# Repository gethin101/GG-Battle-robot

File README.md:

# Gethin's Custom BATTLE ROBOT
**This is my custom Robot Wars inspired battle robot with a servo-driven axe weapon, wireless radio frequency remote control, LCD display, RGB lights, and audio sound effects. My robot is controlled by a custom PCB RF remote using a Raspberry Pi Pico H microcontroller running CircuitPython and the chassis and axe will be 3D printed in PLA.**

It runs on a Raspberry pi pico H, TT motors, L298N motor drivers, and a servo motor. It is controlled by a 433mhz radio frequency remote, another Raspberry pi pico H, a joystick module and extra control buttons. The 2 main axe weapons and chassis will be 3d printed in PLA.

I am also using a 1.8" SPI LCD Display for the robot to display information on the front of the robot and SK6812 MINI-E RGB leds for the back of the robot. These will both be powered by being plugged into the breadboard in the robot using the pins and jumper wires.

Also I have sound effects for my robot. I will do this through a PAM8302 amplifier board and 8Ω 2W speaker. The amplifier board will go into the breadboard & the speaker will plug directly into the PAM8302.

**It is powered by AA batteries, the actual robot will be connected using a breadboard & jumper wires, but I wanted to create a custom PCB for my remote. I designed the PCB in KiCad, also with female sockets so I can remove modules from the remote.**

**Note:** I had to connect the grounds on either side together so they have the same voltage reference point.

My weapon system consists of a servo motor embedded on the underside of the top half of the chassis that will swing the PLA axe weapon down to hit, and back up to rest on the slanted design of the robot.

---

## Inspiration
I wanted to make this project to help me learn CAD design through Fusion 360, PCB design in KiCad and get me into the world of electronics and embedded systems.
I designed my robot with inspiration from Thor in Robot Wars with the axe weapon idea and Apollo with the general shape and aesthetics

---

## Control

I control my robot through the use of the PCB remote. There is a joystick module that with the use of the RF transmitter, will control the TT motors on the robot and therefore the movement of the wheels. 

I have also added a button on the remote to control the servo motor that moves the PLA axe weapon and also a few buttons that play sound effects and display custom data on the display.

---

## **Remote PCB:**

**Solder:**
- Battery wires to copper pad
- Pico through hole
- Buttons

**Headers:**
- RF module
- Joystick
- Boost converter

Remote PCB design:

**This was my first PCB design before I made it in KiCad**

I then designed my remote PCB in KiCad with the schematic below showing how all the components are connected:

**PCB design process:**

I designed my remote PCB in KiCad. I made through-hole pins for the pico where I will have the choice to either solder on female headers which will allow easy removal of the pico for the remote or to directly solder them on. 
This took some time to design as I wasn't sure on which approach would better fit my project, so I left it for my decision when I get the parts.

Next, I added 3 small buttons that I will solder straight onto the PCB. These will be used as control buttons for the robot where I will program them to sent certains signals to the robot, for example to move the axe head up or down with the servo motor, or to carry out pre-programmed movement plans with the TT motors and wheels.

I added two copper pads for the battery+ and battery- to my PCB to power the remote and I ended up decising to put these on the back side of the PCB so it leaves more space on the front and so I can more easily secure the battery pack on the rear side of the remote, with plently of space to move it around before deciding the final position.

I added holes in my PCB where I will solder on female header pins for the radio frequency transmitter device so it can be easily removed if I come across any issues. I repeated this process on different parts of the remote for the joystick device and 5V boost converter to allow for efficient and easy assembly once I'm ready to build my robot. I first went for through-hole pins in my original design but altered it to have header pins as it will be easier to assemble and tinker with.

Next, I added some silkscreen details onto my PCB such as my name, GitHub repo link and a small mechanical logo. This added a bit more personality to my remote and will allow for it to be easier to distinguish from other robots (ik this is only the remote and will most likely be covered later on, but it was fun to mess about with)

I learnt how to add drill holes on the corners of my PCB so it has the option to be secured into a case and therefore will be more comfortable to use with nothing moving about. Furthermore, I also learnt how to make a copper GND pour which I have found out reduces noise on the PCB and allowed me to have better accessibility to the GND on the remote when I was designing and wiring it in KiCad.

I am happy with my remote PCB and I ran the ERC and DRC checkers a few times, fixed all the issues and now it comes up with no errors when I run them.

The KiCad project files & gerber.zip are both in **PCB/** and the PCB cart screenshot from JLCPCB is below

---

## Cart Screenshots

**Here are the cart screenshots for all of my components. I have logged the prices exactly, but there are some discounts and sales on atm that are ending soon so it may end up costing a bit more.**

<details>
<summary>Click to see cart screenshots</summary>

</details>

---

## Components

Here are the lists of components for my robot. I have also made a [full BOM](BOM.md)
with links to all the parts.

**List of components for remote:**

- Raspberry pi pico H
- Joystick module
- 433 MHz transmitter
- 2xAA Battery pack
- Custom PCB for joystick, transmitter, microcontroller, battery input & boost converter
- A few buttons for display, audio & specific movement plans
- Female sockets for component removal
- 5V boost converter

**List of components for robot:**

- Raspberry pi pico H
- 1.8" SPI LCD Display
- SK6812 MINI-E RGBs
- PAM8302 amplifier board
- 8Ω 2W speaker
- 433 MHz receiver
- 2x L298N motor drivers
- 4x TT motors (raw voltage from L298Ns)
- Servo motor
- 6xAA battery pack
- Breadboard
- Jumper wires for wiring
- PLA axe
- 3D printed chassis
- 5V buck converter
- Magnets for top & bottom chassis connection

**My project should cost around $104 so should be tier 2**

---
This was my first hand sketch of the component positioning in my robot but obviously I've changed bits of it

This is a (bit messy) wiring diagram for the robot breadboard system

---

First 3D fusion model of robot chassis:

I originally designed it like this with 2 axe weapons and patterns but have changed to the version below instead.

This version is the final concept for my robot chassis

Rendered robot with textures applied & motors & wheels components

Showing servo motor setup with axe and TT motors

Base bottom of the robot without top half of the chassis

---
# BOM

**Please note that I am requesting $100 and I will pay for the rest myself**

See [BOM](/BOM.csv)

---
**I will make different iterations and designs for the chassis another time but this is my first design for blueprint**

---

## CircuitPython firmware

- I will need to flash [CircuitPython](/Firmware/adafruit-circuitpython-raspberry_pi_pico2-en_GB-10.1.3.uf2) onto my picos
- Install circuitpython libraries .mpys
- Upload the different [code.pys](Firmware/) to my picos
- Test the firmwares are working

# Blueprint requirements

- [✅] A short description of what your project is  
- [✅] A couple of sentences on how to use your project  
- [✅] A couple of sentences on why you made the project  

- [✅ ] Screenshot of a full 3D model of your project  
- [✅ ] Screenshot of your PCB (if applicable)  
- [✅ ] Wiring diagram (if any wiring is not on a PCB)  
- [✅] Bill of Materials (BOM) in table format at the end of the README, with links [BOM](/BOM.csv)

- [✅] Fully original, customized design (not a direct copy of any guide)  
- [✅] Complete CAD assembly including all components (electronics included)  
- [✅] Firmware present (even if untested)  
- [✅] Design sanity‑checked with someone else  approved by [@LoganPeterson](https://hackclub.enterprise.slack.com/team/U079WLY0HLY)

- [✅] BOM in CSV format in the root directory, with links
- [✅] PCB source files (.kicad_pro, .kicad_sch, gerbers.zip, etc.) if applicable  
- [✅] A .STEP file of the full 3D CAD model including electronics  
- [✅] Source CAD files (.f3d, .FCStd, etc., or OnShape public link in README)  
- [✅] All other project files included (firmware, libraries, references, etc.)  
- [✅] Repository organized into readable, logical folders  

> ⚠️ **Important:** Missing a complete .STEP file with all electronics and CAD will result in project rejection. ✅

## 📝 License
This project is open-source under the MIT License and was designed & built during Hackclub Blueprint 2025-26 by [@gethin101](https://github.com/gethin101)

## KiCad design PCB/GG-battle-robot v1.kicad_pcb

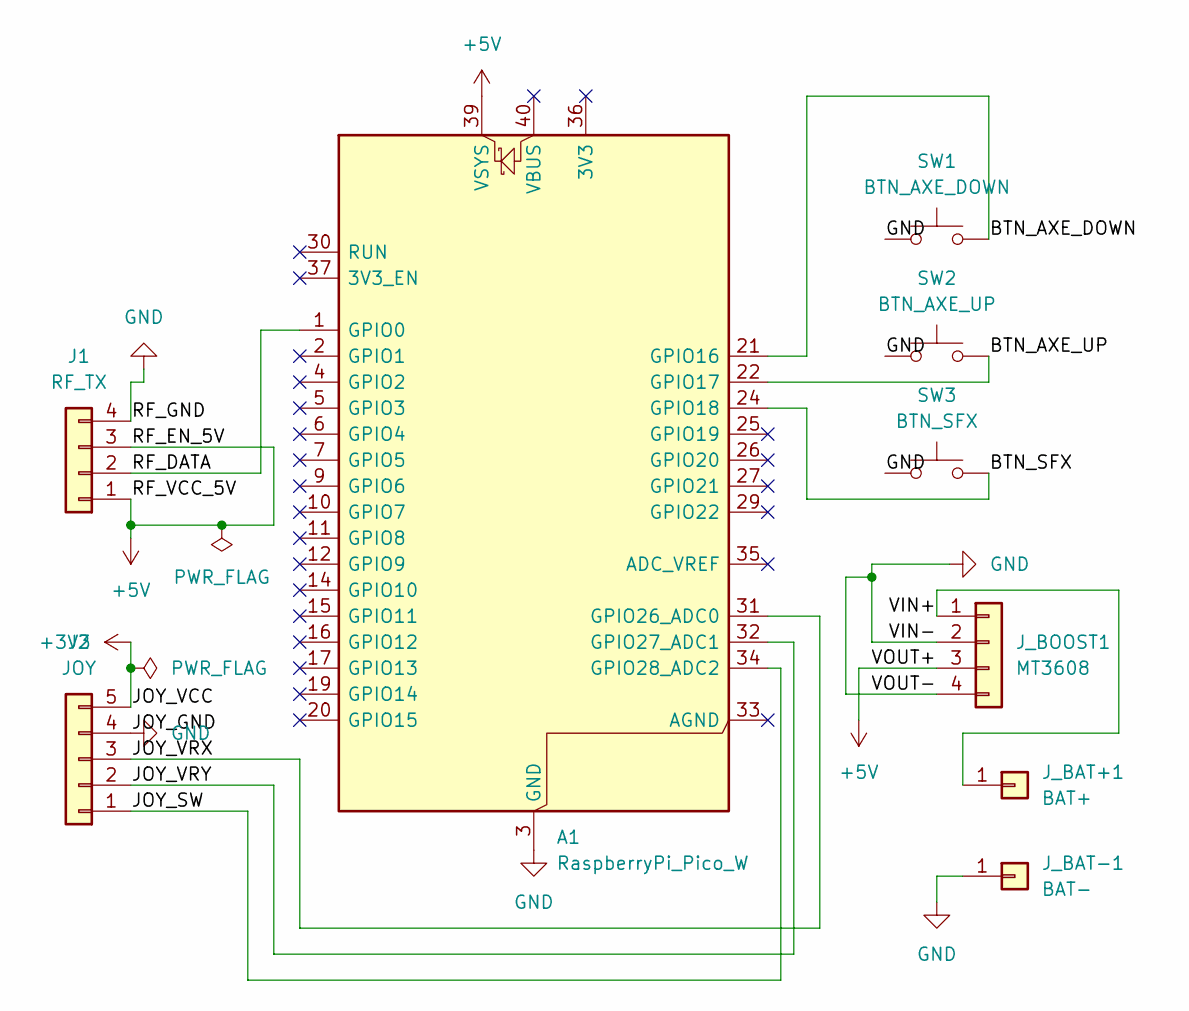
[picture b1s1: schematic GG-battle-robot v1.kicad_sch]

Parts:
A1: RaspberryPi_Pico_W; RaspberryPi_Pico_Common_THT
J1: RF_TX; PinHeader_1x04_P2.54mm_Vertical
J2: JOY; PinHeader_1x05_P2.54mm_Vertical
J_BAT+1: BAT+; SolderWirePad_1x01_SMD_5x10mm
J_BAT-1: BAT-; SolderWirePad_1x01_SMD_5x10mm
J_BOOST1: MT3608; PinHeader_1x04_P2.54mm_Vertical
SW1: BTN_AXE_DOWN; SW_Push_1TS009xxxx-xxxx-xxxx_6x6x5mm
SW2: BTN_AXE_UP; SW_Push_1TS009xxxx-xxxx-xxxx_6x6x5mm
SW3: BTN_SFX; SW_Push_1TS009xxxx-xxxx-xxxx_6x6x5mm

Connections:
+3V3: J2.5
+5V: A1.39 (VSYS), J1.1, J1.3, J_BOOST1.3
/BTN_AXE_DOWN: A1.21 (GPIO16), SW1.2
/BTN_AXE_UP: A1.22 (GPIO17), SW2.2
/BTN_SFX: A1.24 (GPIO18), SW3.2
/JOY_SW: A1.34 (GPIO28_ADC2), J2.1
/JOY_VRX: A1.31 (GPIO26_ADC0), J2.3
/JOY_VRY: A1.32 (GPIO27_ADC1), J2.2
/RF_DATA: A1.1 (GPIO0), J1.2
/VIN+: J_BAT+1.1, J_BOOST1.1
GND: A1.3 (GND), A1.8 (GND), A1.13 (GND), A1.18 (GND), A1.23 (GND), A1.28 (GND), A1.38 (GND), J1.4, J2.4, J_BAT-1.1, J_BOOST1.2, J_BOOST1.4, SW1.1, SW2.1, SW3.1

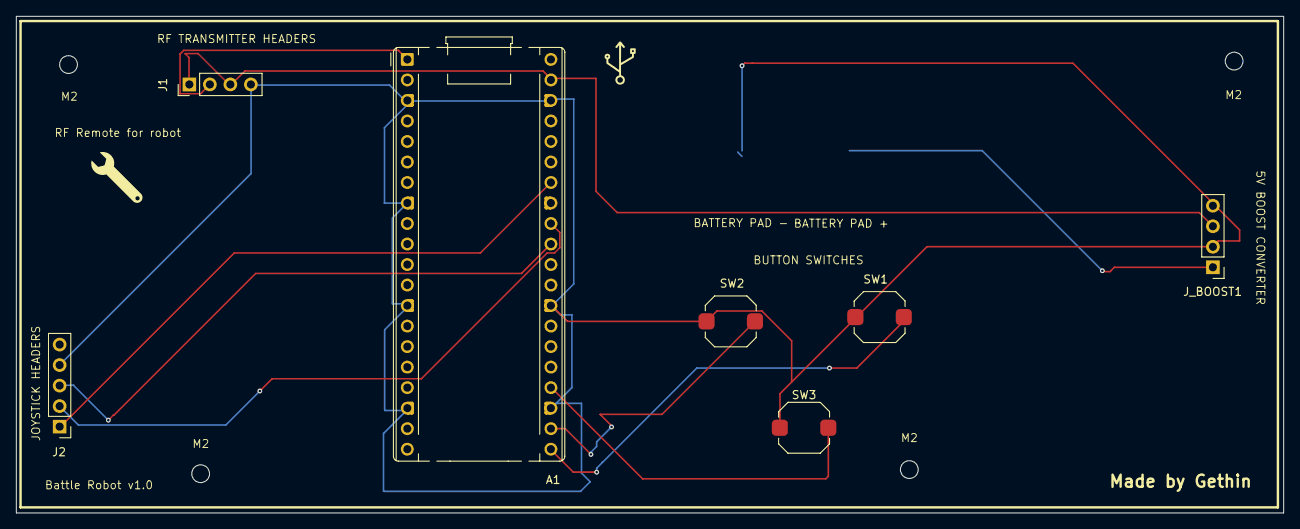
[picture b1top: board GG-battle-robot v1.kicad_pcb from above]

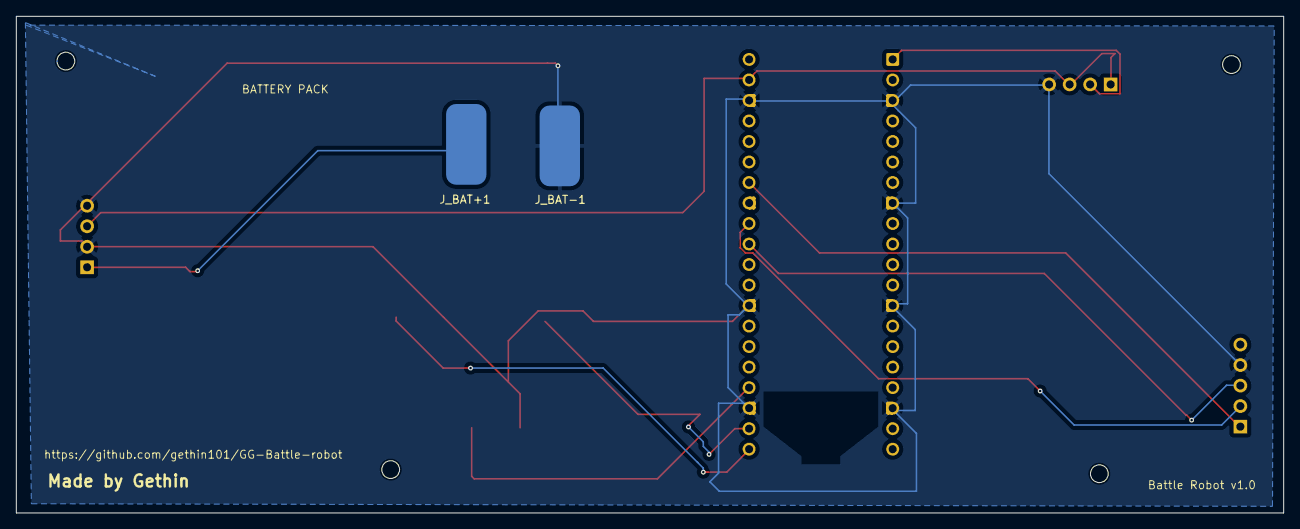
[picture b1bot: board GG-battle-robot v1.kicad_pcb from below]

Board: 2 copper layers, 156.9 x 61.5 mm, 9 parts (2 on the bottom side), 10 nets.

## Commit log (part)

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2025-12-13 Rename IMG_2618.jpeg to Design.png
2025-12-13 Create F
2025-12-14 Rename led.png to led.py
2025-12-14 Rename IMG_2686.jpg to remote_design.png
2025-12-14 Rename Screenshot 2025-12-14 164945.png to robot_fusion1.png
2025-12-18 Create 3D Models
2025-12-18 Create 1
2025-12-18 Rename Screenshot 2025-12-18 184637.png to robot_rendered.png
2025-12-18 Rename Screenshot 2025-12-18 184645.png to robot_design_image.png
2025-12-18 Rename Screenshot 2025-12-18 184702.png to robot_base_image.png
2025-12-19 Rename Screenshot 2025-12-19 170528.png to robot_components_exposed.png
2025-12-19 Rename Screenshot 2025-12-19 170504.png to robot_components.png
2025-12-25 Rename Screenshot 2025-12-24 110527.png to cart1.png
2025-12-25 Rename Screenshot 2025-12-24 110533.png to cart2.png
2025-12-25 Rename Screenshot 2025-12-24 110540.png to cart3.png
2025-12-25 Rename Screenshot 2025-12-24 110545.png to cart4.png
2025-12-25 Rename Screenshot 2025-12-24 110559.png to cart5.png
2025-12-25 Rename Screenshot 2025-12-25 102612.png to cart6.png
2025-12-25 Rename Screenshot 2025-12-25 172439.png to cart1.png
2025-12-25 Rename Screenshot 2025-12-25 172446.png to cart2.png
2025-12-25 Rename Screenshot 2025-12-25 172452.png to cart3.png
2025-12-25 Rename Screenshot 2025-12-25 172458.png to cart4.png
2025-12-25 Rename Screenshot 2025-12-25 172529.png to cart5.png
2025-12-25 Rename Screenshot 2025-12-25 173128.png to cart6.png
2025-12-26 Rename Screenshot 2025-12-26 093709.png to cart7.png
2025-12-26 Rename Screenshot 2025-12-26 091924.png to schem.png
2025-12-26 Rename Screenshot 2025-12-26 092003.png to pcb.png
2026-01-05 Rename Screenshot 2026-01-05 193643.png to cart_pico.png
2026-01-22 Rename Screenshot 2026-01-22 164827.png to cart7.png
2026-01-22 Rename Screenshot 2026-01-22 164827.png to cart8.png
2026-01-22 Rename Screenshot 2026-01-22 170319.png to cart8.png
2026-01-22 Rename Screenshot 2026-01-22 170319.png to cart7.png
2026-01-25 Rename cart7.png to cart_pcb.png
2026-01-25 Rename Screenshot 2026-01-25 134446.png to cart1png
2026-01-25 Rename cart1png to cart1.png
2026-01-25 Rename Screenshot 2026-01-25 134452.png to cart2.png
2026-01-25 Rename Screenshot 2026-01-25 134457.png to cart3.png
2026-01-25 Rename Screenshot 2026-01-25 134501.png to cart4.png
2026-01-25 Rename Screenshot 2026-01-25 134446.png to Cart_1.png
2026-01-25 Rename Screenshot 2026-01-25 134452.png to Cart_2.png
2026-01-25 Rename Screenshot 2026-01-25 134457.png to Cart_3.png
2026-01-25 Rename Screenshot 2026-01-25 134501.png to Cart_4.png
2026-02-11 Revise PCB design process details in README
    Updated the PCB section to provide a detailed overview of the design process, including component choices and design considerations.
2026-02-11 Rename gg-battle-robot-journal.md to journal.md
2026-03-02 Rename Components/Bill-Of-Materials.md to BOM.md
2026-03-05 Rename BOM.md to Images/BOM.md
2026-03-05 Rename Images/BOM.md to BOM.md
2026-03-08 Rename Screenshot 2026-03-08 102439.png to robot_wiring.png
2026-03-08 Rename Firmware/Display/screen.py to Firmware/screen.py
2026-03-08 Rename adafruit-circuitpython-raspberry_pi_pico2-en_GB-10.1.3 (1).uf2 to adafruit-circuitpython-raspberry_pi_pico2-en_GB-10.1.3.uf2
2026-03-09 Rename BOM.csv to Images/BOM.csv
2026-03-15 Rename Screenshot 2026-03-15 085137.png to top_slicer.png
2026-05-04 Rename 1.py to web_AP.py
2026-05-09 Rename Firmware/AP/robot_working-reverse.py to Firmware/AP/1/robot_working-reverse.py
